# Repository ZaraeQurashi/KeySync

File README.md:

# KeySync — Custom MIDI Controller

A custom-built MIDI controller inspired by Undertale, featuring seven heart-shaped capacitive touch keys, two mechanical pushbuttons, and a rotary encoder.

KeySync combines custom PCB design, programming, and game inspired aesthetics to create a unique musical  device. The heart-shaped touch pads are inspired by the 7 SOULS from the game UNDERTALE, giving the controller a recognizable design while serving as its main musical input.

---

## Table of Contents

- [Project Overview](#project-overview)
- [Hardware](#hardware)
- [PCB Design](#pcb-design)
- [Controls and Key Mapping](#controls-and-key-mapping)
- [Firmware](#firmware)
  
---

## Project Overview

KeySync started as an idea for a custom MIDI controller that would combine my interests in electronics, programming, and video games. Instead of using a standard keyboard layout, I wanted to design something with a distinct appearance that reflected the games that inspired it.

The project involved designing the circuit in KiCad, arranging components on a custom PCB, creating heart-shaped copper electrodes for the touch keys, routing the board, developing the firmware, and documenting the parts required to build it.

One of the main goals was to make the controller visually interesting while still keeping the controls practical. The seven touch keys provide the main musical input, the mechanical pushbuttons add two extra notes, and the rotary encoder provides a convenient way to control system volume.

### Project Details

| Category | Details |
|---|---|
| Project name | KeySync |
| Project type | Custom MIDI controller |
| Microcontroller | Seeed Studio XIAO ESP32-S3 |
| PCB design software | KiCad |
| Firmware language | Python |
| Firmware environment | CircuitPython |
| Keyboard framework | KMK |
| Main inputs | 7 capacitive touch pads |
| Additional inputs | 2 mechanical pushbuttons |
| Encoder | 1 rotary encoder |
| Design inspiration | UNDERTALE |

## Hardware

KeySync is built around the Seeed Studio XIAO ESP32-S3 microcontroller. The board acts as the controller for the inputs and runs the firmware that determines how the device responds to them.

The hardware consists of three main input groups.

### 1. Capacitive Touch Keys

The seven heart-shaped electrodes are the main controls on KeySync. They are designed to detect touch and correspond to individual notes in a C-major scale.

Unlike a mechanical switch, a capacitive touch key doesn't require a physical contact to close a circuit. Instead, the sensing system detects a change in capacitance when a finger approaches or touches the electrode.

### 2. Mechanical Pushbuttons

KeySync also includes two low-profile mechanical pushbuttons. These provide additional physical inputs that can be used alongside the touch keys. 

The firmware assigns each button a separate drum note, allowing them to trigger additional sounds or percussion samples in compatible MIDI software. The buttons use GPIO inputs configured with pull-ups, with the inputs changing state when the buttons connect their respective pins to ground.

### 3. Rotary Encoder

The rotary encoder provides a control that can be turned in either direction. In the current firmware configuration, it is intended to adjust the computer's system volume.

---

## PCB Design

The PCB was designed in KiCad. After completing the schematic, I moved on to arranging the components, creating the board outline, designing the custom heart-shaped electrodes, and routing the electrical connections.

### Schematic and Component Placement

The schematic defined the electrical connections between the microcontroller and the various inputs. Once the schematic was ready, I transferred the components into the PCB layout and began arranging them to fit the board.

During this stage, I encountered footprint sizing issues and had to adjust an oversized footprint to fit the available space. I also revised some schematic connections and custom footprint pad numbers to make sure the PCB layout matched the intended electrical connections.

This reinforced the importance of checking the physical dimensions of components and the electrical mapping of their pads.

### Routing

After settling on the component placement, I routed the PCB using both copper layers.

- **F.Cu — Front copper:** Used for routing the capacitive touch key connections.
- **B.Cu — Back copper:** Used for routing the mechanical switch connections.

Using both layers helped organize the traces and make better use of the available board space.

## Controls and Key Mapping

The firmware is configured to map the seven touch keys to a C-major scale, the two mechanical buttons to drum notes, and the rotary encoder to system volume control.

### Capacitive Touch Keys

| Touch key | MIDI note number | Intended note |
|---|---:|---|
| Heart 1 | 60 | C4 |
| Heart 2 | 62 | D4 |
| Heart 3 | 64 | E4 |
| Heart 4 | 65 | F4 |
| Heart 5 | 67 | G4 |
| Heart 6 | 69 | A4 |
| Heart 7 | 71 | B4 |

### Mechanical Pushbuttons

| Button | MIDI note number | Intended use |
|---|---:|---|
| Button 1 | 36 | Drum/percussion trigger |
| Button 2 | 38 | Drum/percussion trigger |

### Rotary Encoder

| Control | Function |
|---|---|
| Rotary encoder | Increase or decrease computer system volume |
| Communication method | Media-key commands in the current firmware design |

---

## Firmware

The firmware is written in Python using CircuitPython and KMK. It handles input scanning, maps the controls to their intended functions, and provides the logic needed for the controller to respond to touches, button presses, and encoder movements.

### Firmware Structure

The code is organized around several main responsibilities:

**Touch sensing:** Reads the state of the seven capacitive touch inputs and detects changes between touched and untouched states.

**Button scanning:** Reads the two mechanical pushbuttons and determines when they are pressed or released.

**Key mapping:** Associates each touch key and pushbutton with its assigned MIDI note.

**Encoder controls:** Reads the rotary encoder and triggers the appropriate system volume command.

### GPIO Pin Mapping

The following GPIO assignments are from the current firmware configuration.

| Control | GPIO pin |
|---|---|
| Capacitive touch key 1 | GPIO3 |
| Capacitive touch key 2 | GPIO4 |
| Capacitive touch key 3 | GPIO5 |
| Capacitive touch key 4 | GPIO6 |
| Capacitive touch key 5 | GPIO7 |
| Capacitive touch key 6 | GPIO8 |
| Capacitive touch key 7 | GPIO9 |
| Mechanical pushbutton 1 | GPIO43 |
| Mechanical pushbutton 2 | GPIO44 |
| Rotary encoder signal A | GPIO1 |
| Rotary encoder signal B | GPIO2 |

### MIDI Behaviour

The seven touch keys are intended to send MIDI note events corresponding to the C-major scale. Touching a key triggers a Note On event, while releasing it triggers a matching Note Off event.

The two mechanical pushbuttons are assigned to notes 36 and 38 for percussion.

---

## Challenges and Lessons Learned

Developing KeySync involved more than creating a circuit board. Some of the most important work happened while adapting the firmware and making sure the software matched the hardware.

### PCB Design Challenges

Creating the PCB required me to design custom heart-shaped electrodes, fit the components within the board outline, fix an oversized footprint, and revise pad numbers and connections. Routing the switches and touch keys across two copper layers also required careful planning.

These challenges taught me to check both the physical and electrical sides of a design. A footprint can look correct on screen but still be unsuitable for the actual component, and an attractive layout is not useful if the pads do not connect to the intended signals.

### Firmware Compatibility

I initially explored an Arduino-based firmware approach and encountered compatibility problems involving USB MIDI classes, MIDI event types, and capacitive touch functions. I eventually moved to CircuitPython and KMK, which meant adapting the implementation instead of simply transferring the earlier code.

This taught me that code written for one development environment does not automatically work in another. Microcontroller features, library APIs, and USB support can differ significantly between boards and programming environments.

---

## Final Summary

KeySync brought together my interests in electronics, programming and gaming into one custom MIDI controller inspired by UNDERTALE. From designing the PCB and seven heart-shaped capacitive touch keys in KiCad to developing the CircuitPython/KMK firmware, creating the BOM, and documenting everything on GitHub, I gained hands-on experience with both hardware and software. Although troubleshooting firmware compatibility was challenging, it taught me to approach problems systematically and consider how every part of a project works together. Overall, KeySync helped me better understand the process of turning an idea into a custom electronic device.

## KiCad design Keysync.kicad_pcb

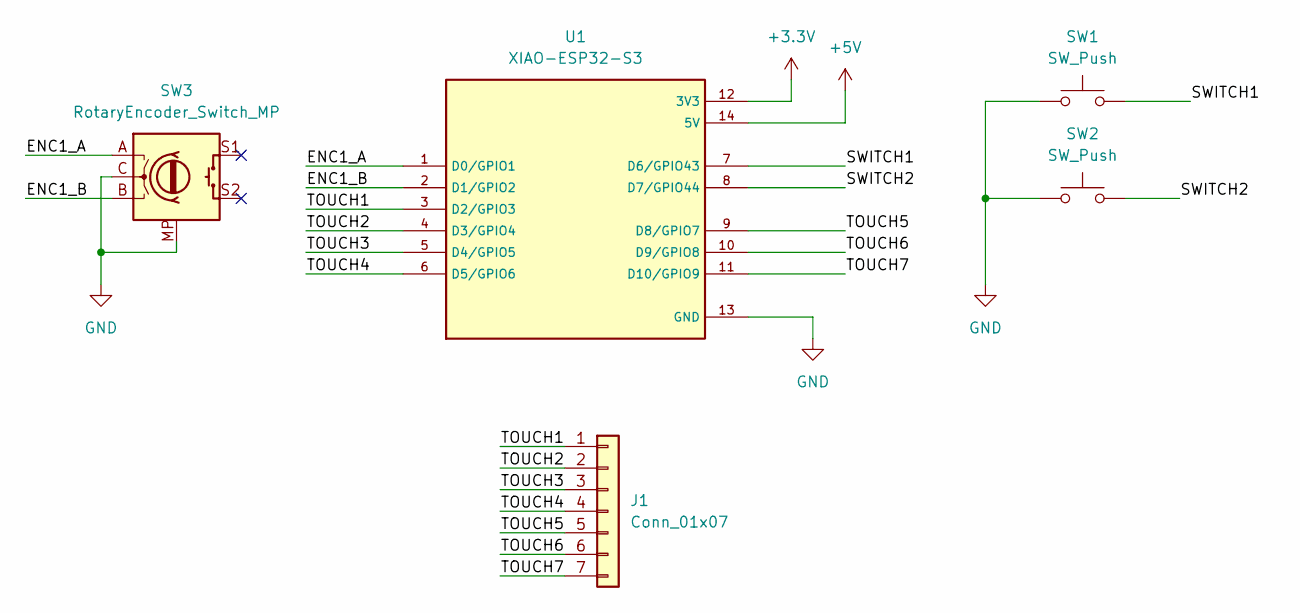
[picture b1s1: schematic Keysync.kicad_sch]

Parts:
J1: Conn_01x07; Capacitative Keys Heart
SW1, SW2: SW_Push; Kailh Choc Low-Profile Switches
SW3: RotaryEncoder_Switch_MP; RotaryEncoder_Alps_EC11E-Switch_Vertical_H20mm
U1: XIAO-ESP32-S3; XIAO ESP32-S3; PARTREV April 22nd, 2026

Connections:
+3.3V: U1.12 (3V3)
+5V: U1.14 (5V)
/ENC1_A: SW3.A, U1.1 (D0/GPIO1)
/ENC1_B: SW3.B, U1.2 (D1/GPIO2)
/SWITCH1: SW1.2, U1.7 (D6/GPIO43)
/SWITCH2: SW2.2, U1.8 (D7/GPIO44)
/TOUCH1: J1.1, U1.3 (D2/GPIO3)
/TOUCH2: J1.2, U1.4 (D3/GPIO4)
/TOUCH3: J1.3, U1.5 (D4/GPIO5)
/TOUCH4: J1.4, U1.6 (D5/GPIO6)
/TOUCH5: J1.5, U1.9 (D8/GPIO7)
/TOUCH6: J1.6, U1.10 (D9/GPIO8)
/TOUCH7: J1.7, U1.11 (D10/GPIO9)
GND: SW1.1, SW2.1, SW3.C, SW3.MP, U1.13 (GND)

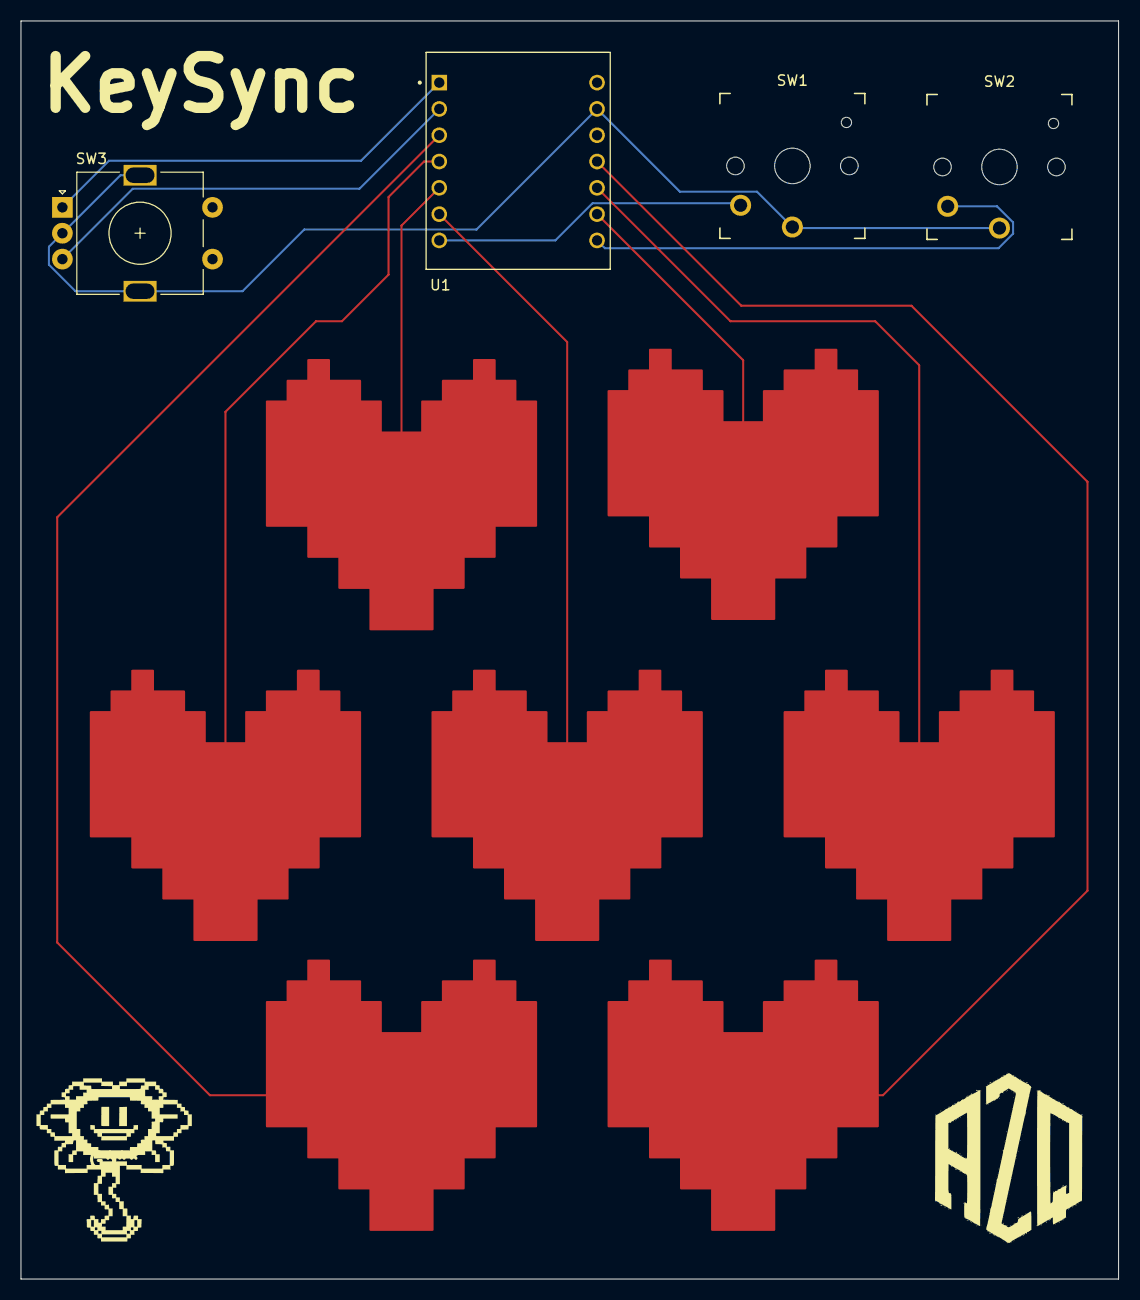
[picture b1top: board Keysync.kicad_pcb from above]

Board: 2 copper layers, 106.0 x 121.5 mm, 5 parts (0 on the bottom side), 12 nets.

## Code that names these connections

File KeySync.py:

# KeySync MIDI Controller
# 7 capacitive touch keys, 2 switches, 1 rotary encoder
# Board: Seeed Studio XIAO ESP32-S3

import keypad
import touchio
from microcontroller import pin

from kmk.extensions.media_keys import MediaKeys
from kmk.keys import KC
from kmk.kmk_keyboard import KMKKeyboard
from kmk.modules.encoder import EncoderHandler
from kmk.modules.midi import MidiKeys
from kmk.scanners import Scanner
from kmk.scanners.keypad import KeysScanner


# Custom scanner for capacitive touch pads
class TouchScanner(Scanner):
    def __init__(self, pins):
        self.pads = [touchio.TouchIn(p) for p in pins]
        self.pressed = [False] * len(pins)

    @property
    def key_count(self):
        return len(self.pads)

    def scan_for_changes(self):
        for i, pad in enumerate(self.pads):
            touched = pad.value

            if touched != self.pressed[i]:
                self.pressed[i] = touched
                return keypad.Event(i + self.offset, touched)

        return None


# Initialize keyboard and extensions
keyboard = KMKKeyboard()

midi = MidiKeys()
media_keys = MediaKeys()


# Input configuration
keyboard.matrix = [
    # 7 capacitive touch pads: GPIO3-GPIO9
    TouchScanner([
        pin.GPIO3,
        pin.GPIO4,
        pin.GPIO5,
        pin.GPIO6,
        pin.GPIO7,
        pin.GPIO8,
        pin.GPIO9,
    ]),

    # 2 physical switches: GPIO43 and GPIO44
    KeysScanner(
        [pin.GPIO43, pin.GPIO44],
        value_when_pressed=False,
        pull=True,
    ),
]


# Key mappings
keyboard.keymap = [[
    # Touch pads: C major scale
    KC.MIDI_NOTE(60),  # C4
    KC.MIDI_NOTE(62),  # D4
    KC.MIDI_NOTE(64),  # E4
    KC.MIDI_NOTE(65),  # F4
    KC.MIDI_NOTE(67),  # G4
    KC.MIDI_NOTE(69),  # A4
    KC.MIDI_NOTE(71),  # B4

    # Switches: drum sounds
    KC.MIDI_NOTE(36),  # Kick drum
    KC.MIDI_NOTE(38),  # Snare drum
]]


# Rotary encoder: GPIO1 and GPIO2
encoder = EncoderHandler()

encoder.pins = (
    (pin.GPIO1, pin.GPIO2, None),
)

encoder.map = [
    ((KC.VOLD, KC.VOLU, KC.NO),),
]

# Register modules and extensions
keyboard.modules = [
    midi,
    encoder,
]

keyboard.extensions = [
    media_keys,
]

# Start the controller
if __name__ == "__main__":
    keyboard.go()
